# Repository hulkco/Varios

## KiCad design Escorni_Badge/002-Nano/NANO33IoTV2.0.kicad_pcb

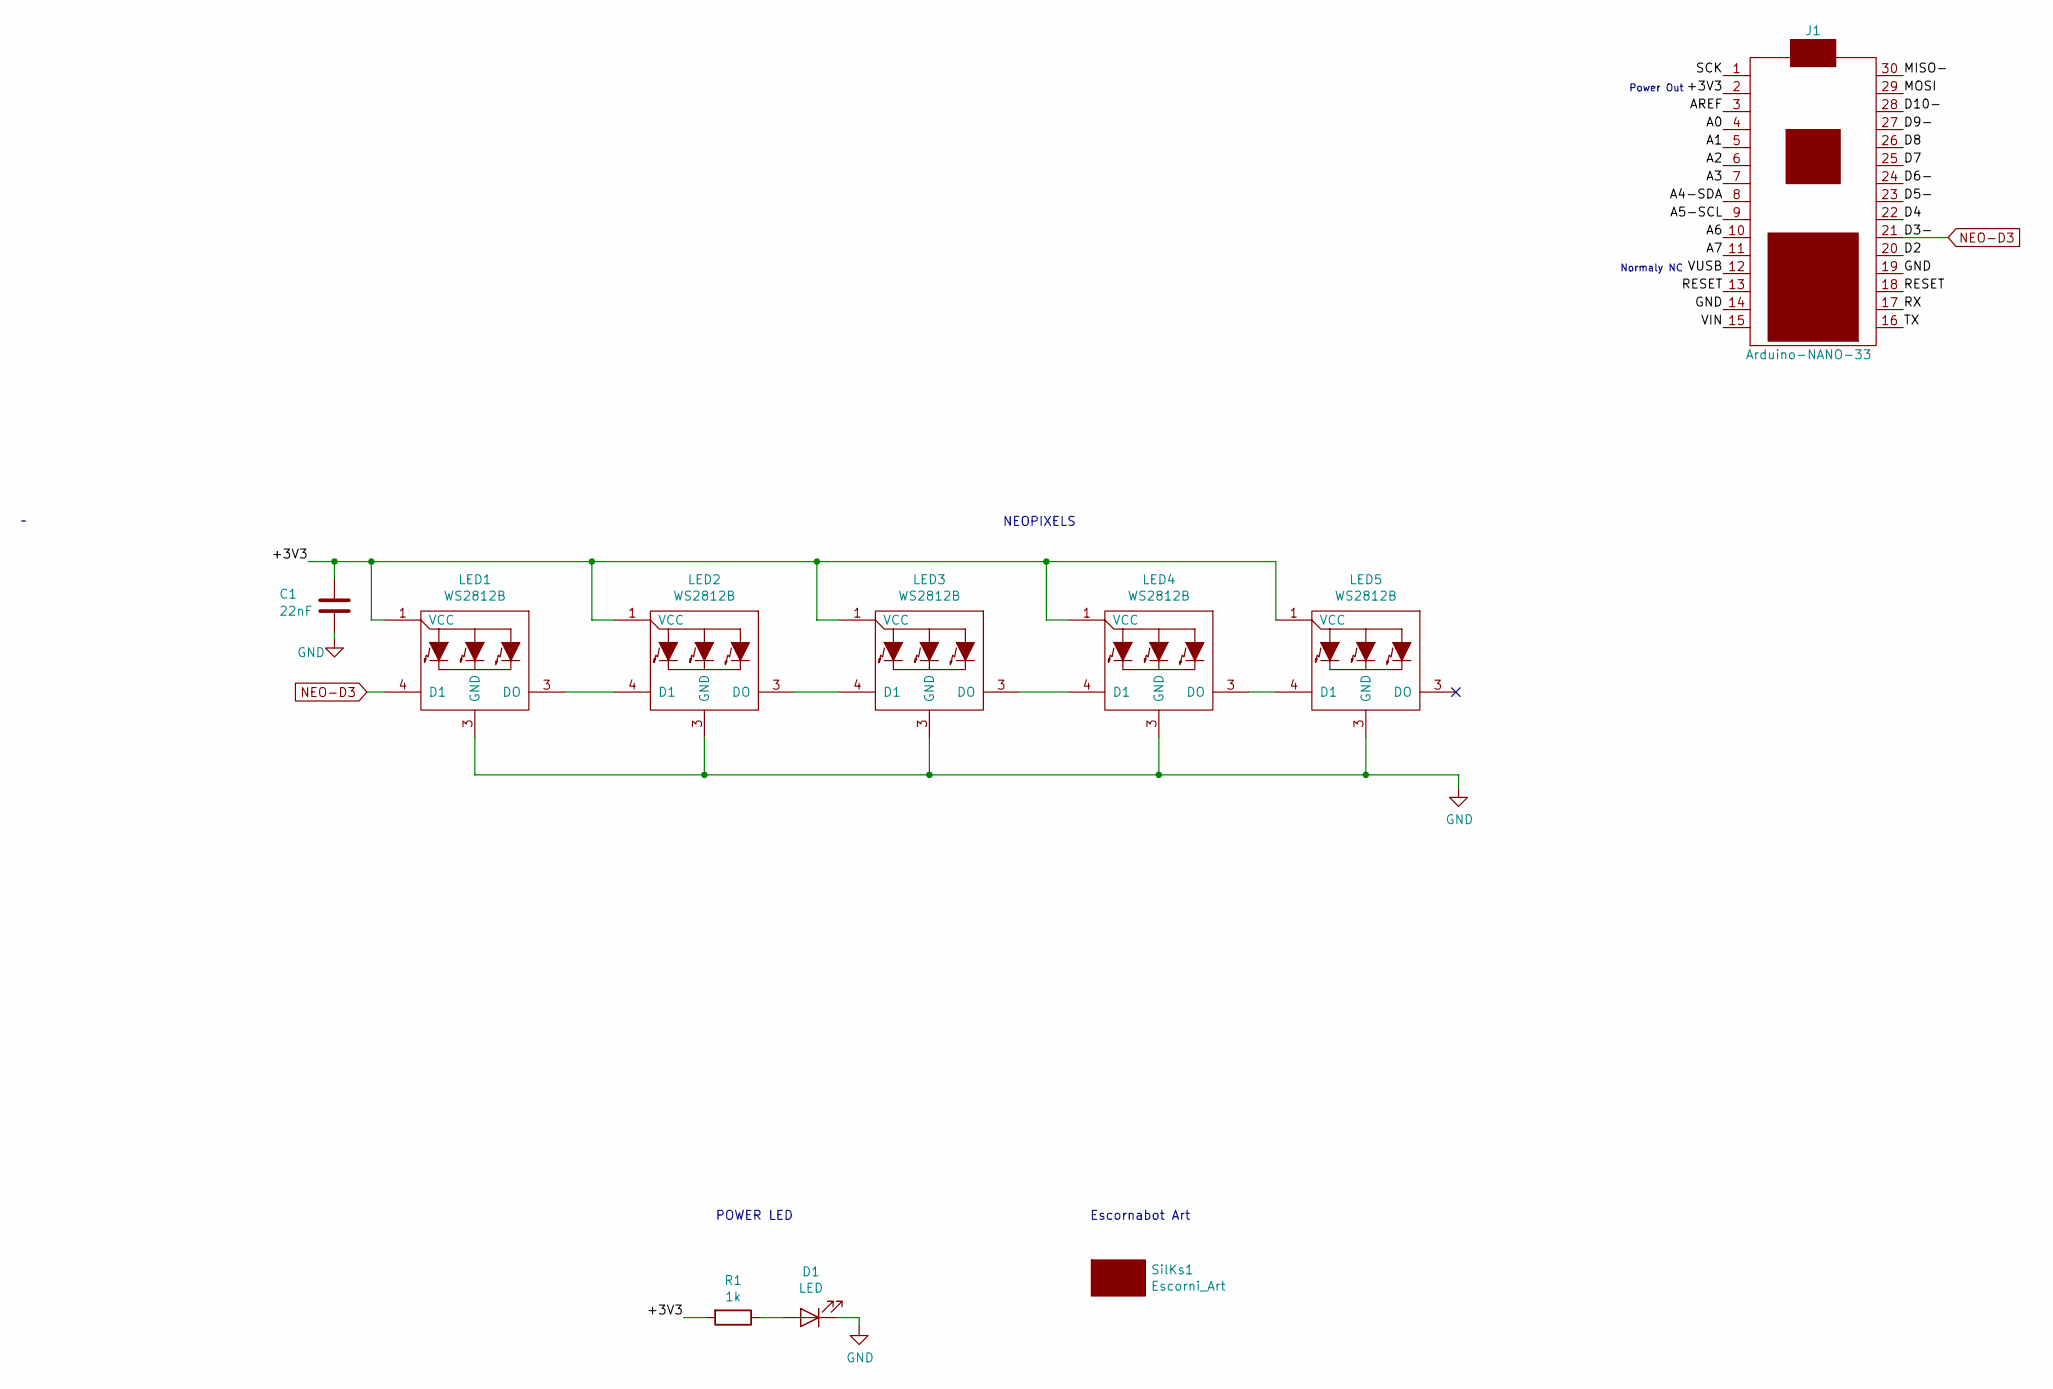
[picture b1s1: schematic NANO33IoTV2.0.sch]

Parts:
C1: 22nF; C_0805_2012Metric_Pad1.15x1.40mm_HandSolder
D1: LED; LED_0805_2012Metric_Pad1.15x1.40mm_HandSolder
J1: Arduino-NANO-33; NANO_33_Single_Socket
LED1, LED2, LED3, LED4, LED5: WS2812B
R1: 1k; R_0805_2012Metric_Pad1.15x1.40mm_HandSolder
SilKs1: Escorni_Art; escorni-badge-new_05_Nano_100mm

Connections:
/+3V3: C1.1, J1.2, LED1.1 (VCC), LED2.1 (VCC), LED3.1 (VCC), LED4.1 (VCC), LED5.1 (VCC), R1.2
/A0: J1.4
/A1: J1.5
/A2: J1.6
/A3: J1.7
/A4-SDA: J1.8
/A5-SCL: J1.9
/A6: J1.10
/A7: J1.11
/AREF: J1.3
/D2: J1.20
/D4: J1.22
/D5-: J1.23
/D6-: J1.24
/D7: J1.25
/D8: J1.26
/D9-: J1.27
/D10-: J1.28
/MISO-: J1.30
/MOSI: J1.29
/RESET: J1.13, J1.18
/RX: J1.17
/SCK: J1.1
/TX: J1.16
/VIN: J1.15
/VUSB: J1.12
NEO-D3: J1.21, LED1.4 (D1)
unnamed: D1.2 (A), R1.1

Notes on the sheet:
NEOPIXELS
POWER LED
Escornabot Art
Power Out
Normaly NC

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
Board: 4 copper layers, 10 parts (0 on the bottom side), 9 nets, no tracks yet.

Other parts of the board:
Ref**: Val**; escorni-badge-new_06_Nano_100mm

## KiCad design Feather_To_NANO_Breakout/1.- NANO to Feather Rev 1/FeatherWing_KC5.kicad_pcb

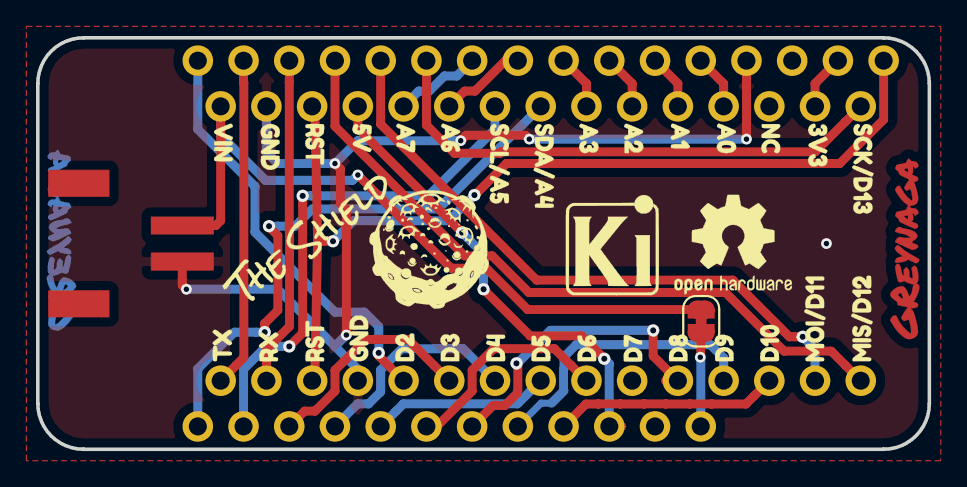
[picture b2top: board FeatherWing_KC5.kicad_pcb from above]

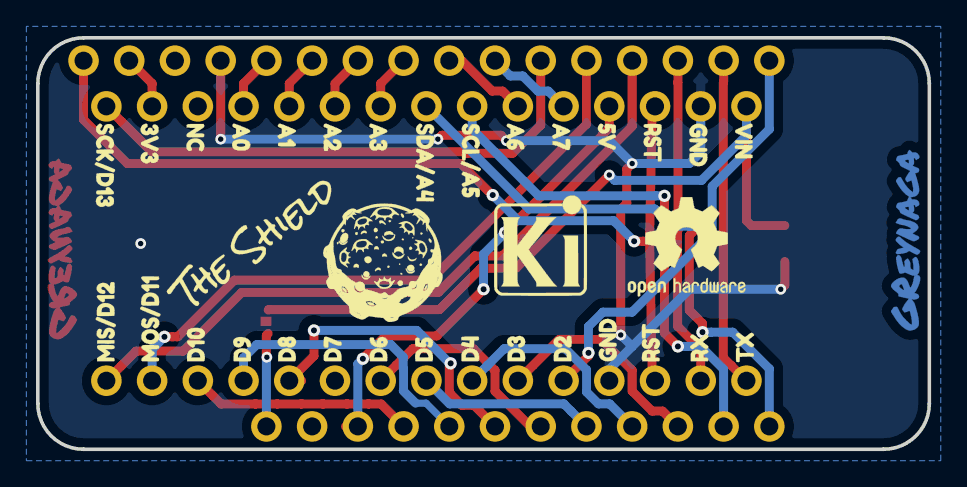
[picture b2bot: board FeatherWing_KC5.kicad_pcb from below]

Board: 2 copper layers, 49.5 x 22.9 mm, 17 parts (7 on the bottom side), 27 nets.

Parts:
J1: feather long; PinHeader_1x16_P2.54mm_Vertical
J2: feather short; PinHeader_1x12_P2.54mm_Vertical
J3, J4: Conn_01x15; PinSocket_1x15_P2.54mm_Vertical
J5: Conn_01x02; JST-PH_S2B-PH-SM4-TB
JP1: Jumper_NC_Small; SolderJumper-2_P1.3mm_Bridged_RoundedPad1.0x1.5mm
U1, U7: Feather_Cu; Feather_CU
U2: Feather_Silks
U3, U8: KiCadLogo; Ki-2500
U4, U9: Moon_Firma; Moon_Firma_SilkS
U5, U10: Feather_Silks; Moon_The_Shield_SilkS
U6, U11: KiCadLogo; OSHW-Logo2_7.3x6mm_SilkScreen

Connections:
+3V3: J1.15, J4.14
+5V: J2.10, J4.4
/A0: J1.12, J4.12
/A1: J1.11, J4.11
/A2: J1.10, J4.10
/A3: J1.9, J4.9
/A6: J1.8, J4.6
/A7: J1.7, J4.5
/D2: J1.1, J3.5
/D3: J2.3, J3.6
/D4: J2.4, J3.7
/D5: J2.5, J3.8
/D6: J2.6, J3.9
/D8: J2.7, J3.11
/D9: J2.8, J3.12
/D10: J2.9, J3.13
/D11-MOSI: J1.5, J3.14
/D12-MISO: J1.4, J3.15
/RX: J1.3, J3.2
/SCK-D13: J1.6, J4.15
/SCL-A5: J2.2, J4.7
/SDA-A4: J2.1, J4.8
/TX: J1.2, J3.1
/VIN: J4.1, J5.1, JP1.1
/~RESET: J1.16, J3.3, J4.3
GND: J1.13, J3.4, J4.2, J5.2
unnamed: J2.12, JP1.2
